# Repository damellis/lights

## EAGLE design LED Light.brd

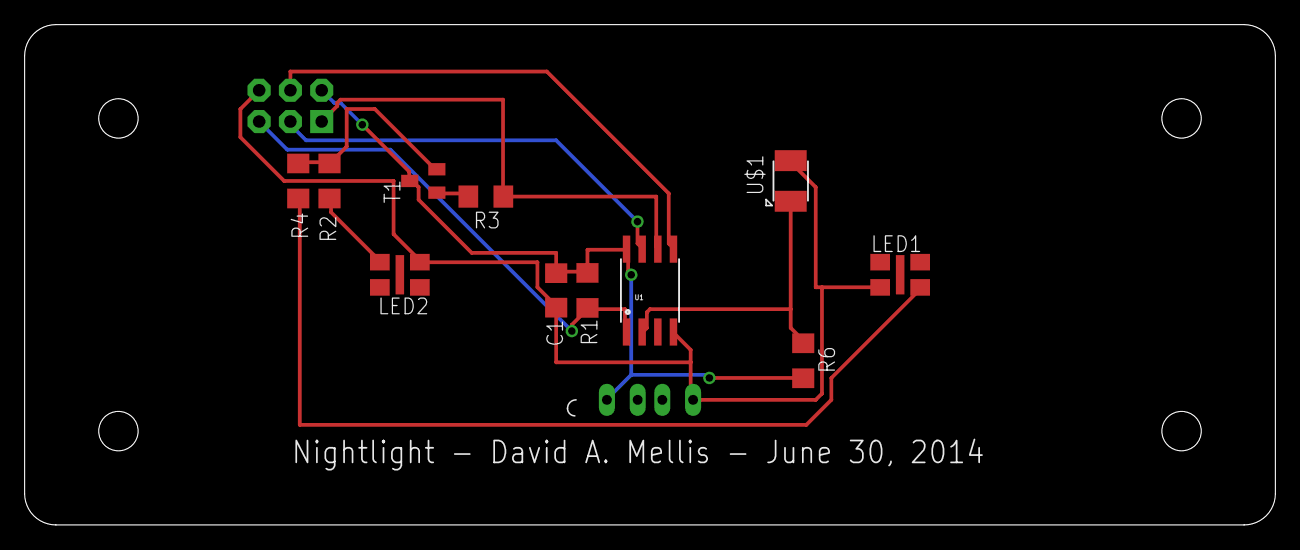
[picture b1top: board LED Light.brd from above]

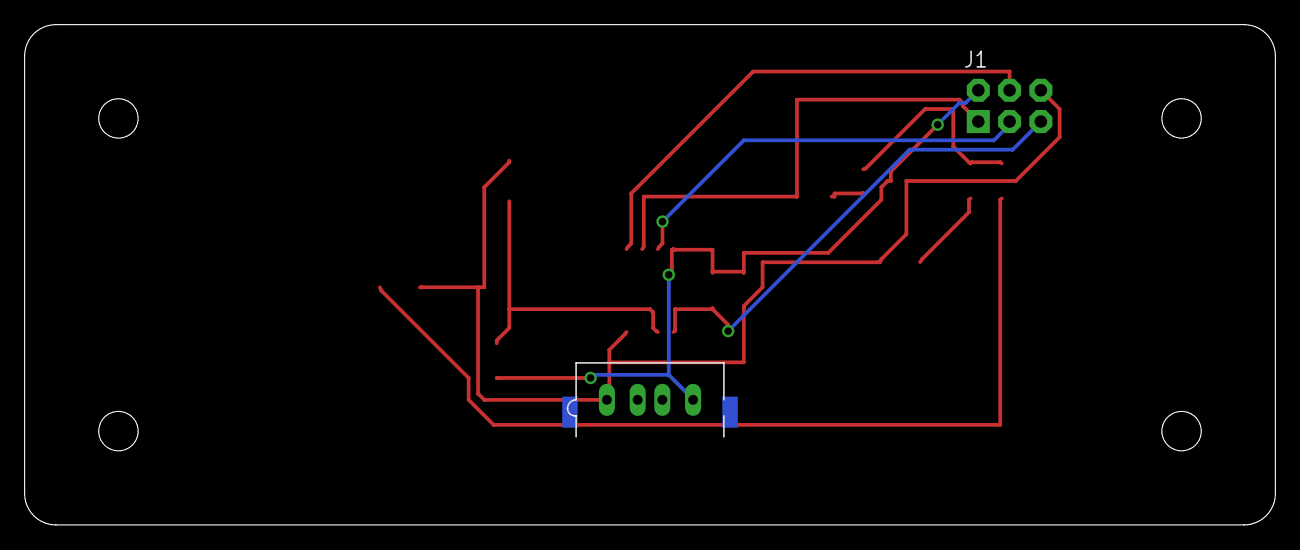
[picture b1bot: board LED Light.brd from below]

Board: 2 copper layers, 101.6 x 40.6 mm, 13 parts (2 on the bottom side), 11 nets.

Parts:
C1: 1.0uF; C1206
J1: AVR_SPI_PRG_6NS; 2X3-NS
JP1: USB_A_VERTICAL
LED1, LED2: ML-EFAB; ML-E-FAB
R1: 10K; R1206
R2, R4: 24; R1206
R3: 1K; R1206
R6: 49.9K; R1206
T1: SOT23-BEC
U1: Tiny85-20-SMT; SO08-EIAJ
U$1: PHOTOTRANSISTOR-NPN-OP580AD; OP580DA

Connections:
GND: C1.2, J1.6, JP1.GND, LED1.C@1, LED2.C@1, U1.4, U$1.EMITTER
MISO: J1.1, R3.1, U1.6
MOSI: J1.4, U1.5
unnamed: R2.2, R4.2, T1.E
unnamed: R3.2, T1.B
unnamed: LED2.A@1, R2.1
unnamed: LED1.A@1, R4.1
unnamed: R6.1, U1.2, U$1.COLLECTOR
RESET: J1.5, R1.1, U1.1
SCK: J1.3, U1.7
VCC: C1.1, J1.2, JP1.VBUS, R1.2, R6.2, T1.C, U1.8

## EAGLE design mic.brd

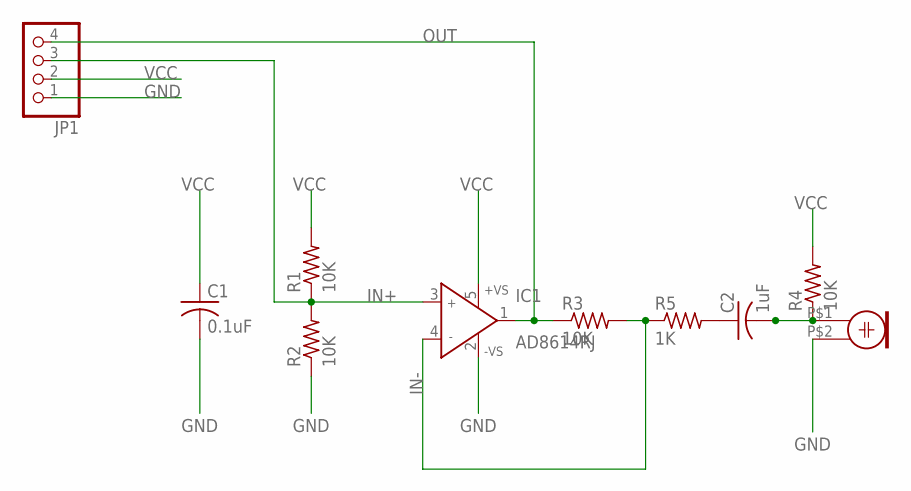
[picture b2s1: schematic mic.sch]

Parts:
C1: 0.1uF; C1206
C2: 1uF; C1206
IC1: AD8614RJ; SOT23-5
JP1: PINHD-1X4; 1X04
R1, R2, R3, R4: 10K; R1206
R5: 1K; R1206
U$1: ELECTRET; ELECTRET_6MM_SMD

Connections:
GND: C1.2, IC1.2 (-VS), JP1.1, R2.1, U$1.P$2 (2)
IN+: IC1.3 (IN+), JP1.3, R1.1, R2.2
IN-: IC1.4 (IN-), R3.2, R5.1
unnamed: C2.1, R5.2
unnamed: C2.2, R4.1, U$1.P$1 (1)
OUT: IC1.1 (OUT), JP1.4, R3.1
VCC: C1.1, IC1.5 (+VS), JP1.2, R1.2, R4.2

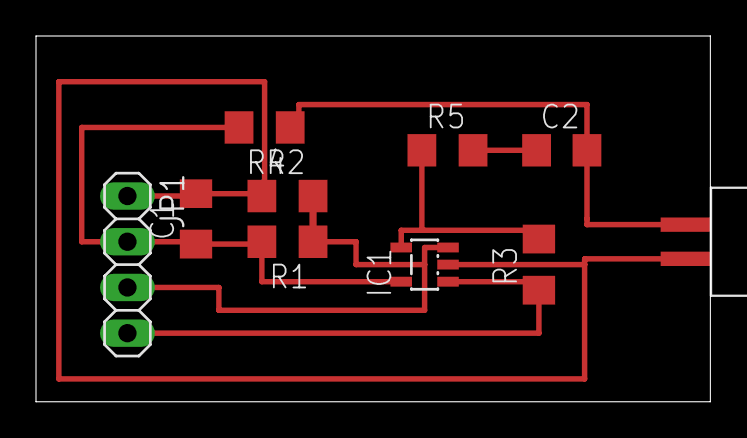
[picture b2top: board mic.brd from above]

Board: 2 copper layers, 37.5 x 20.3 mm, 10 parts (0 on the bottom side), 7 nets.

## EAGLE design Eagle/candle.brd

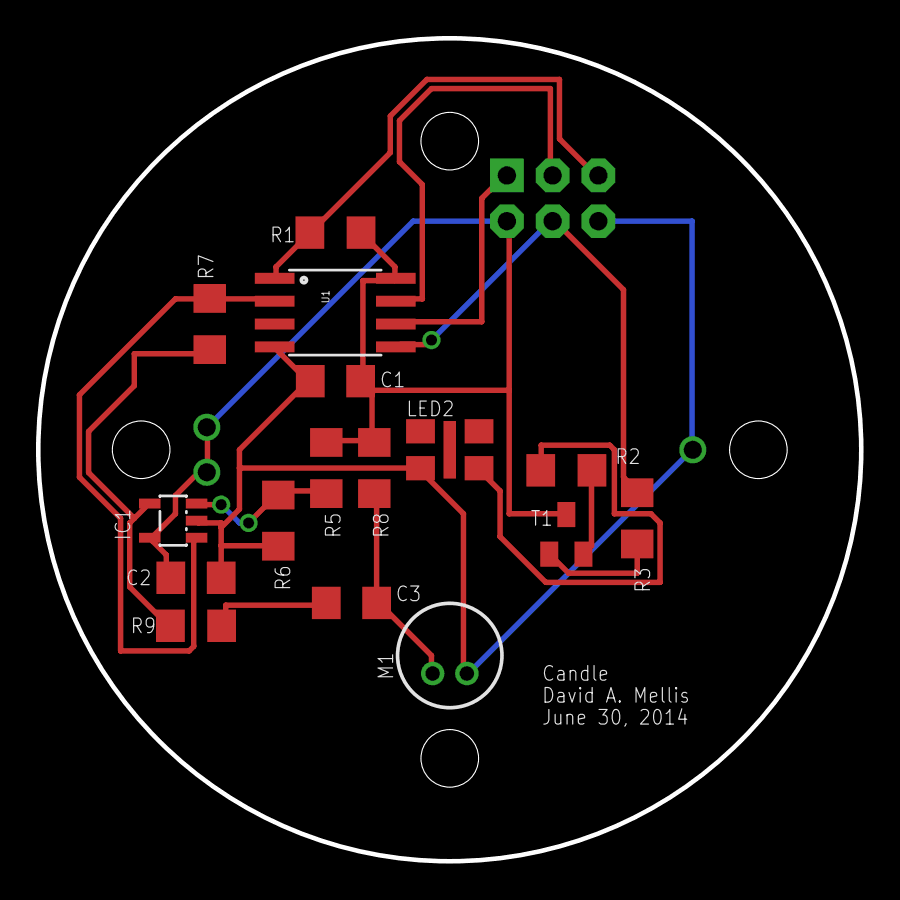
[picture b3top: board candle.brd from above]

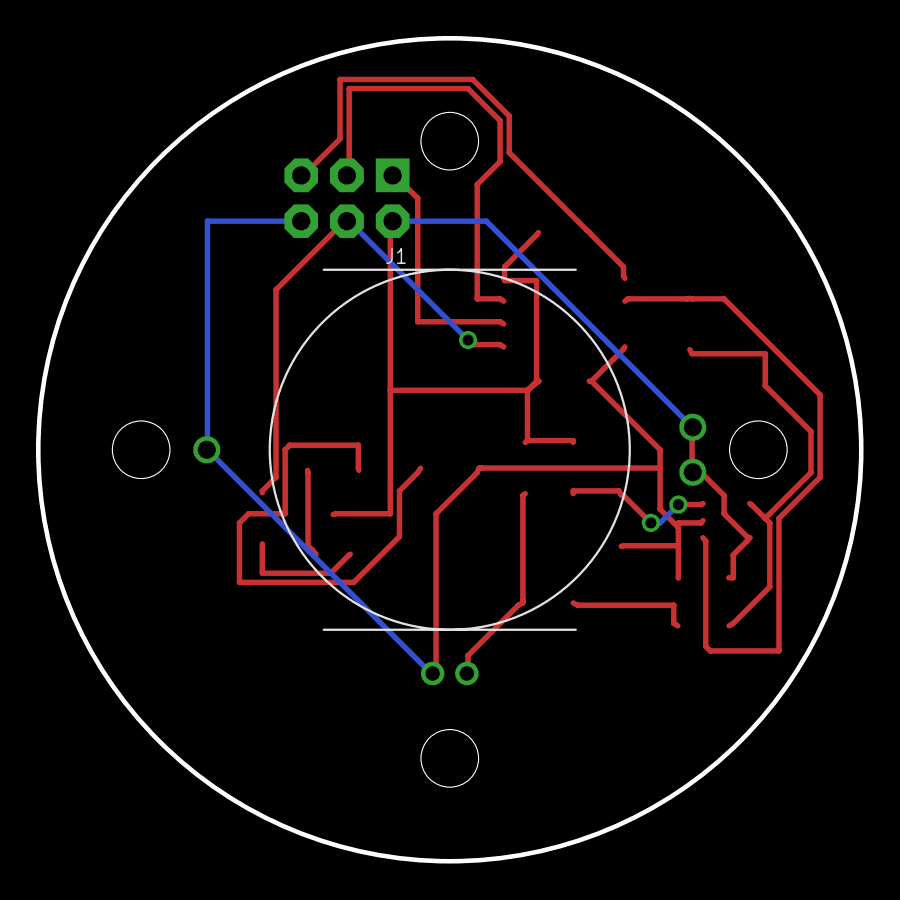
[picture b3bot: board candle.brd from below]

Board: 2 copper layers, 45.7 x 45.7 mm, 18 parts (2 on the bottom side), 14 nets.

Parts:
C1: 1.0uF; C1206
C2: 0.1uF; C1206
C3: 1uF; C1206
IC1: AD8615AUJZ; SOT23-5
J1: AVR_SPI_PRG_6NS; 2X3-NS
LED2: ML-EFAB; ML-E-FAB
M1: ELECTRETTH; ELECTRET_6MM_TH
R1, R5, R6, R7, R8: 10K; R1206
R2: 24; R1206
R3, R9: 1K; R1206
T1: SOT23-BEC
U1: Tiny85-20-SMT; SO08-EIAJ
U$1: BATTERY-CR2032; CR2032_TH

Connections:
GND: C1.2, C2.2, IC1.2, J1.6, LED2.C@1, M1.2, R6.1, U1.4, U$1.-
IN+: IC1.3, R5.1, R6.2
IN-: IC1.4, R7.2, R9.1
MIC: IC1.1, R7.1, U1.2
MISO: J1.1, U1.6
MOSI: J1.4, R3.1, U1.5
unnamed: R2.2, T1.E
unnamed: R3.2, T1.B
unnamed: LED2.A@1, R2.1
unnamed: C3.2, M1.1, R8.1
unnamed: C3.1, R9.2
RESET: J1.5, R1.1, U1.1
SCK: J1.3, U1.7
VCC: C1.1, C2.1, IC1.5, J1.2, R1.2, R5.2, R8.2, T1.C, U1.8, U$1.+, U$1.+'

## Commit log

2014-05-16 Initial prototype: ATtiny45/85, 1206 LEDs, and a mini-USB jack.
2014-05-16 Light-bulb-shaped board, reverse-mount LEDs, and SMT AVR ISP header.
2014-05-19 Add 10M resistor and traces for capacitive sensing.
2014-05-19 Update document layer and PNG images for milling.
2014-06-02 Finish initial version of Pac Man board. Generate PNGs for milling.
2014-06-02 Add Eagle library with some custom parts.
2014-06-02 Create layer for acrylic and generate pdf.
2014-06-02 Update acrylic layer: use circular cutout around LED.
2014-06-04 Add layer for the yellow vinyl sticker (for Pac-Man's body).
2014-06-04 Add second acrylic layer and generate corresponding PDF files.
2014-06-05 Night-light lamp, including PNGs for milling and PDFs for laser-cutting.
2014-06-05 Remove leftover PDF.
2014-06-06 Move components and re-route board for double-sided PCB.
2014-06-06 Re-layout board for PCB fabrication (two layers). Add mounting holes.
2014-06-06 Add mounting holes. Redraw acrylic base layer in Eagle board file.
2014-06-09 Initial work on board layout. Still missing mic circuit.
2014-06-09 Add firmware for nightlight and test program.
2014-06-10 Replace Mini-B USB connector w/ male A. Switch LEDs to PB1 (MISO). Layout.
2014-06-11 Tweak board layout, generate PNGs for milling.
2014-06-11 Ignore Eagle backup files.
2014-06-11 Modify acrylic layers and generate PDFs.
2014-06-11 Fix symmetry of acrylic base and regenerate PDF.
2014-06-11 Move LEDs to PWM pin (MOSI) and clean up layout.
2014-06-11 Breakout board for electret mic.
2014-06-12 Breakout board and PNGs for electret mic circuit.
2014-06-13 Update frame of acrylic base; regenerate PDF.
    Make the frame uniform thickness on all sides, round its corners.
2014-06-13 Integrate mic into main board, layout in circle.
2014-06-13 Update pin number and delay in Arduino code.
2014-06-16 Tweaks to board layout and mic footprint.
2014-06-16 Add acrylic layers. Export PNGs for milling.
2014-06-17 Update acrylic layers and generate PDFs.
2014-06-17 Arduino firmware for mic testing and candle.
2014-06-19 Board w/ accelerometer and LiPo charging circuit.
2014-06-19 Firmware for toggling LED when jar shakes.
2014-06-23 Un-mirror USB connector.
2014-06-30 Replace non-standard parts, two-sided layout, silk
2014-06-30 Remove obsolete PDFs and PNGs.
2014-06-30 Remove unrelated Arduino nightlight sketches.
2014-06-30 Add drill holes; update design rules.
2014-06-30 Generate gerbers.
2014-06-30 Add holes; silk layout; route for two-layers.
2014-06-30 Generate berbers (and label board).
2014-06-30 Remove old PNGs for milling.
2014-06-30 Tweak silk and generate gerbers.
2014-06-30 Add holes; re-route; generate gerbers.
    For two-layer board.
2014-06-30 Move drills holes and silk; new gerbers.
2014-06-30 Add Digi-Key part number for coin cell holder.
2014-06-30 Regenerate Gerbers.
    Move outline to its own layer. Add bottom silk screen.
2014-06-30 Remove blank bottom silk file from Gerber zip.
2014-06-30 Update Gerbers (separate outline, bottom silk).
2014-06-30 Regenerate Gerbers.
2014-06-30 Add missing Gerber file.
2014-06-30 Remove old Gerber zip file.
2014-07-02 New Gerbers (for AP Circuits)
2014-07-07 Create alternative acrylic base layout (and PDF).
2014-07-08 Night light firmware w/ analogWrite() for dimming
2014-07-08 Combine branches into one branch.
2014-07-11 Add BOM and Eagle files for individual modules.
2014-10-05 Adjust light sensor threshold for new component.

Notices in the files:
parts and their libraries:
SparkFun-DigitalIC: Licensing: Creative Commons ShareAlike 4.0 International - https://creativecommons.org/licenses/by-sa/4.0
